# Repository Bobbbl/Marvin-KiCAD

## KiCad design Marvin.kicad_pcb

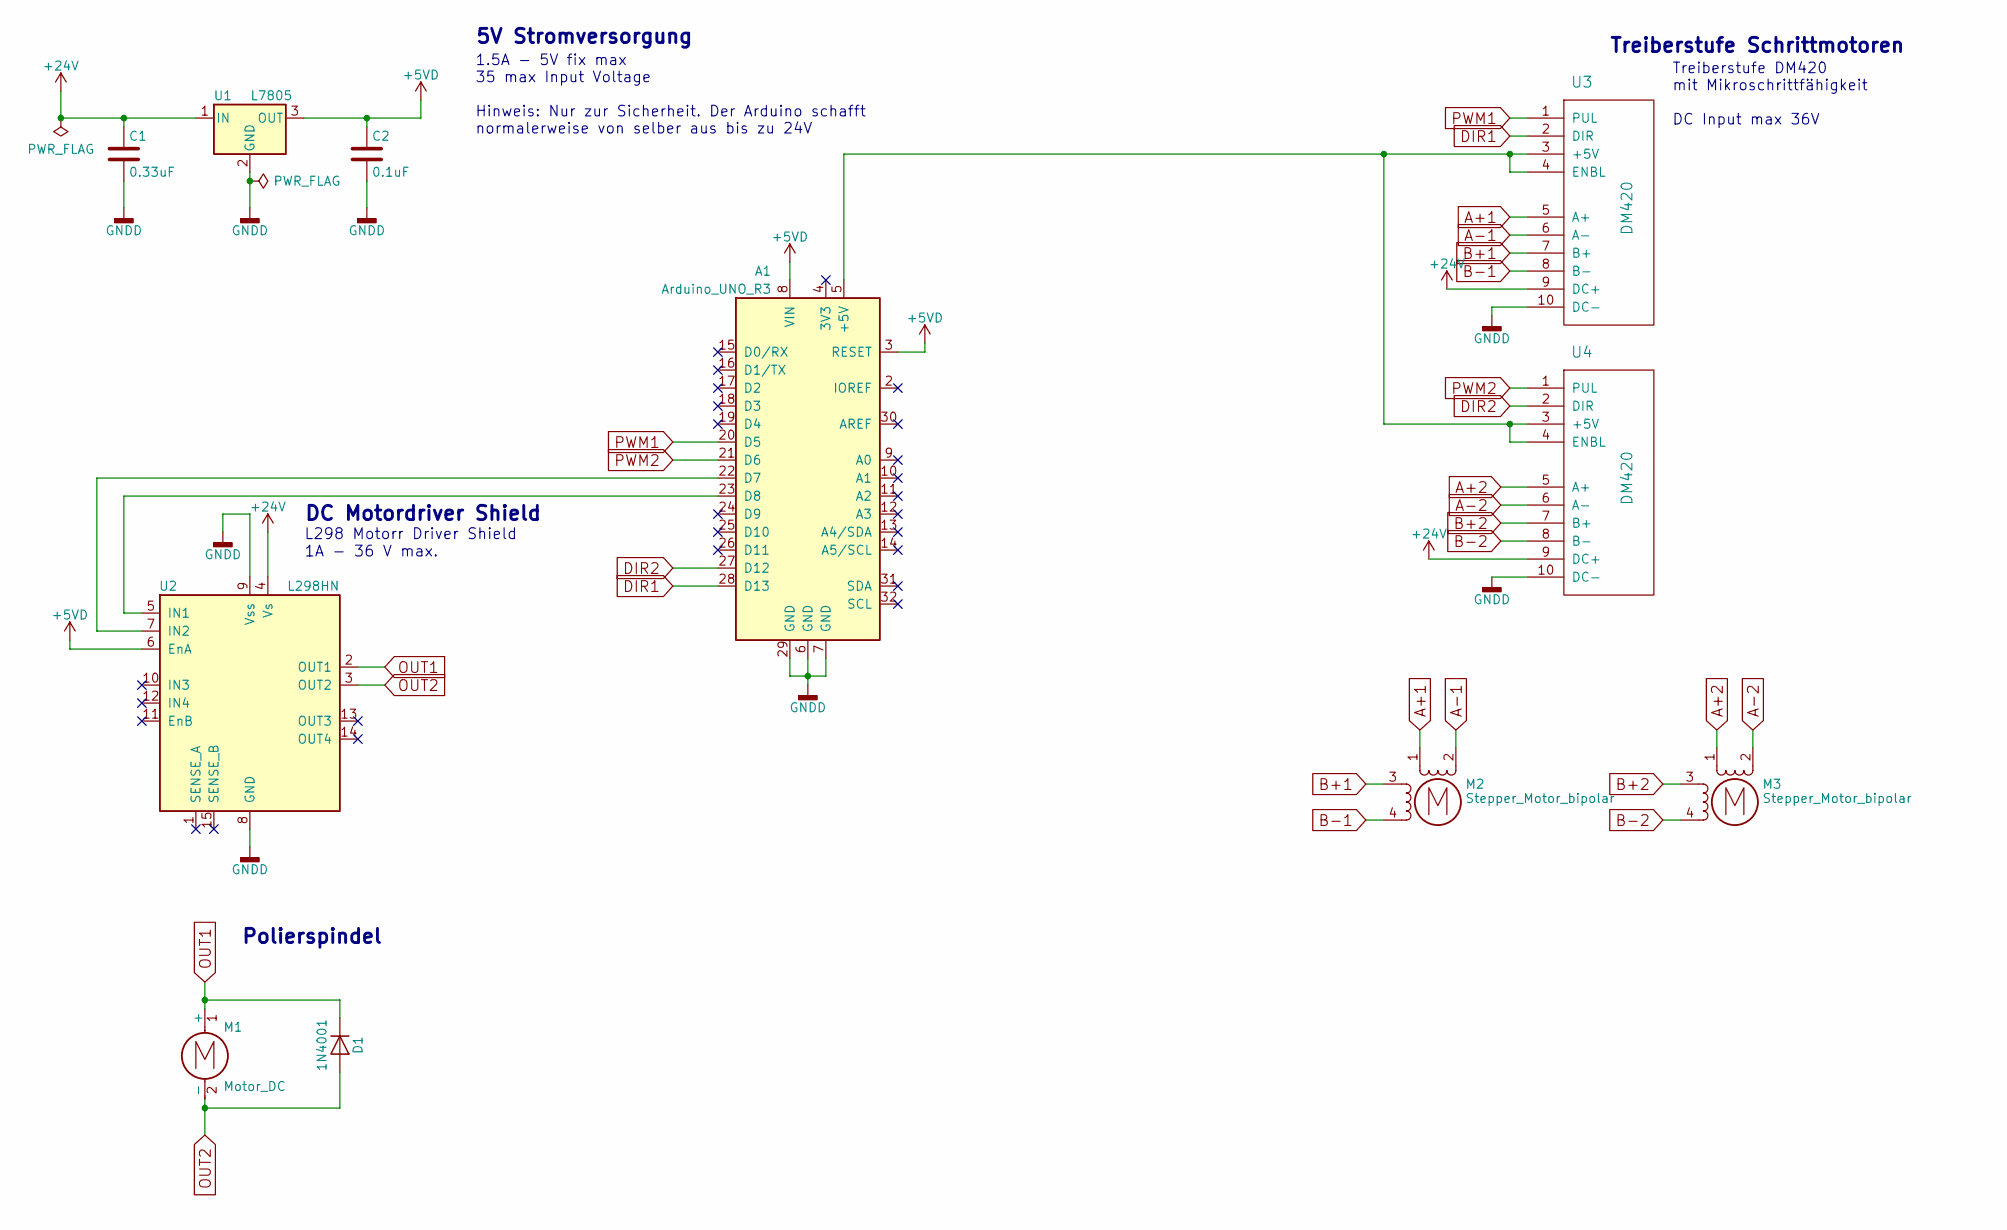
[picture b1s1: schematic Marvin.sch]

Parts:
A1: Arduino_UNO_R3; Arduino_UNO_R3_WithMountingHoles
C1: 0.33uF; C_Rect_L7.5mm_W6.5mm_P5.00mm
C2: 0.1uF; C_Rect_L7.5mm_W6.5mm_P5.00mm
D1: 1N4001; D_DO-41_SOD81_P2.54mm_Vertical_AnodeUp
M1: Motor_DC; TerminalBlock_Phoenix_MKDS1.5-2pol
M2, M3: Stepper_Motor_bipolar; TerminalBlock_Phoenix_MKDS1.5-4pol
U1: L7805; TO-220
U2: L298HN; TO-220-15_P2.54x2.54mm_StaggerOdd_Lead4.58mm_Vertical
U3, U4: DM420; TerminalBlock_Phoenix_MPT-2.54mm_10pol

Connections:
+5VD: A1.3 (RESET), A1.8 (VIN), C2.1, U1.3 (OUT), U2.6 (EnA)
+24V: C1.1, U1.1 (IN), U2.4 (Vs), U3.9 (DC+), U4.9 (DC+)
A+1: M2.1, U3.5 (A+)
A+2: M3.1, U4.5 (A+)
A-1: M2.2 (-), U3.6 (A-)
A-2: M3.2 (-), U4.6 (A-)
B+1: M2.3, U3.7 (B+)
B+2: M3.3, U4.7 (B+)
B-1: M2.4, U3.8 (B-)
B-2: M3.4, U4.8 (B-)
DIR1: A1.28 (D13), U3.2 (DIR)
DIR2: A1.27 (D12), U4.2 (DIR)
GNDD: A1.6 (GND), A1.7 (GND), A1.29 (GND), C1.2, C2.2, U1.2 (GND), U2.8 (GND), U2.9 (Vss), U3.10 (DC-), U4.10 (DC-)
unnamed: A1.5 (+5V), U3.3 (+5V), U3.4 (ENBL), U4.3 (+5V), U4.4 (ENBL)
unnamed: A1.23 (D8), U2.5 (IN1)
unnamed: A1.22 (D7), U2.7 (IN2)
OUT1: D1.1 (K), M1.1 (+), U2.2 (OUT1)
OUT2: D1.2 (A), M1.2 (-), U2.3 (OUT2)
PWM1: A1.20 (D5), U3.1 (PUL)
PWM2: A1.21 (D6), U4.1 (PUL)

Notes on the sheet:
Polierspindel
DC Motordriver Shield
L298 Motorr Driver Shield 1A - 36 V max.
5V Stromversorgung
1.5A - 5V fix max 35 max Input Voltage Hinweis: Nur zur Sicherheit. Der Arduino schafft normalerweise von selber aus bis zu 24V
Treiberstufe Schrittmotoren
Treiberstufe DM420 mit Mikroschrittfähigkeit DC Input max 36V

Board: 2 copper layers, 10 parts (0 on the bottom side), 18 nets, no tracks yet.

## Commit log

2018-11-13 Exchanged Arduino Uno to Arduino Mega 2560 and added SD Card Module
2018-11-13 Limit Switches und Rotary Encoders hinzugefuegt.
2018-11-14 Added MC Description in Schematic
2018-11-15 Updatet PWM Outputs matching Timer 3 and 4
2019-02-05 Removed Rescue lib
2019-02-27 Kleine Aktualisierung
2019-03-01 Aktualisierung Raspberry Pi und Zellen
2019-03-05 PWM 3 nachgetragen
2019-03-06 Relay Modul
    Releis Modul nachgetragen
2019-03-06 Kommentar
    Kommentar bei Releis Modul nachgetragen
2019-03-13 IN1 & IN2 ausgetauscht mit DIR1 & DIR2

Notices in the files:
Marvin.sch:
License: ---
